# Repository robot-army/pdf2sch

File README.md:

# pdf2sch

Convert PDF schematics into KiCad schematics with a human-in-the-loop review loop.

## Current MVP

This repository now includes a minimal executable pipeline in `pdf2sch.py` that:

- Detects symbols/wires/text from a PDF source via a pluggable detector interface (placeholder for CV + OCR + ML)
- Filters likely sheet border/title block text
- Builds a structured component list + netlist
- Maps components to KiCad library symbols/footprint hints
- Prioritizes netlist correctness by asking review questions for low-confidence nets
- Generates KiCad schematic text output
- Preserves multi-page and hierarchical-sheet metadata in the generated schematic
- Uses a `PipelineConfig` object (uconfig-style declarative configuration) so detection/review/mapping rules can be tuned without changing core pipeline flow

## Run

```bash
cd <your-local-clone>/pdf2sch
python pdf2sch.py
```

Enter a PDF path or URL when prompted (for example the CN0359 PDF URL from the issue statement).

## Test

```bash
cd <your-local-clone>/pdf2sch
python -m unittest discover -s tests -v
```

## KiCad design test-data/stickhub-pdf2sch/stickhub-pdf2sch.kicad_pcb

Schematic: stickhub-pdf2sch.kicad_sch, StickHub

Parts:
C1: 1uF 10V; 1005_C; Voltage 16V; Tolerance 10%
C2, C5, C6, C7, C8, C9, C10, C11, C12, C13: 0.1uF; 1005_C; Voltage 16V; Tolerance 10%
C3, C4: 10uF 6.3V; 1005_C; Voltage 16V; Tolerance 10%
C14, C15, C16, C17, C18, C19, C20, C21: 0.1uF 100V; 2012_C; Voltage 16V; Tolerance 10%
C22, C23, C24, C25, C26, C27, C29, C30, C31, C32, C33, C34, C35, C36, C37: 22uF 10V; 1608_C; Voltage 16V; Tolerance 10%
C28: 15nF; 1005_C; Voltage 16V; Tolerance 10%
C38: 330uF 10V; CP_Elec_6.3x11_Board_Edge_Mirrored
D1, D2, D3, D4, D5, D6, D7, D8, D9, D10, D11, D12, D13, D14, D22, D23: TVS; D_0402; MPN AR0521P1
D15, D16, D17, D18, D19, D20, D21: USB; Duo_LED_1.6x0.8_Kingbright_APHB1608LZGKSURKC; MPN APHB1608SGEC
D24, D25: 5V; D_0402; MPN D5V0H1B2LP-7B
H1: Strap; Plain_Hole_3mm
J1: HOST; USB_A_PCB_traces_small
J2: USB1; JST_SH_SM04B-SRSS-TB_1x04-1MP_P1.00mm_Horizontal; MPN SM04B-SRSS-TB(LF)(SN)
J3: USB2; JST_SH_SM04B-SRSS-TB_1x04-1MP_P1.00mm_Horizontal; MPN SM04B-SRSS-TB(LF)(SN)
J4: USB3; JST_SH_SM04B-SRSS-TB_1x04-1MP_P1.00mm_Horizontal; MPN SM04B-SRSS-TB(LF)(SN)
J5: USB4; JST_SH_SM04B-SRSS-TB_1x04-1MP_P1.00mm_Horizontal; MPN SM04B-SRSS-TB(LF)(SN)
J6: USB5; JST_SH_SM04B-SRSS-TB_1x04-1MP_P1.00mm_Horizontal; MPN SM04B-SRSS-TB(LF)(SN)
J7: USB6; JST_SH_SM04B-SRSS-TB_1x04-1MP_P1.00mm_Horizontal; MPN SM04B-SRSS-TB(LF)(SN)
J8: USB7; JST_SH_SM04B-SRSS-TB_1x04-1MP_P1.00mm_Horizontal; MPN SM04B-SRSS-TB(LF)(SN)
J9: EXTGND; 1P-1.5x1.5
JP1: EXTPWR; JP-2_1.5x1.5
LOGO1: Logo; Creative_Commons_CC_Mask
LOGO2: Logo; Creative_Commons_BY_Mask
LOGO3: Logo; Creative_Commons_NC_Mask
LOGO4: Logo; Creative_Commons_SA_Mask
R1: 10k; R_1005_C; MPN 0402WGF1002TCE
R2, R3, R4, R5: 100k; R_1005_C; MPN 0402WGF1003TCE
R6: 2.7k; R_1005_C; MPN 0402WGF2701TCE
R7, R8, R9, R10, R11, R12, R13: 470; R_1005_C; MPN 0402WGF4700TCE
U1: MaxLinear_XR22417-48; LQFP-48_7x7mm_P0.5mm; MPN XR22417CV48TR-F
U2: Dialog_SLG5NT1487V; TDFN-8_1.5x2mm_Fused-Lead_JEDEC_MO-252_W2015D; MPN SLG5NT1487VTR
Y1: 12MHz 50ppm 16-20pF; Crystal_4-SMD_2.5x2mm; MPN CM4012M00020T8188026

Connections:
+1V8: C4.1, C11.1, C12.1, C13.1, U1.6 (VCC18), U1.21 (VCC18), U1.25 (1V8_OUT), U1.28 (VCC18)
+3.3V: C3.1, C5.1, C6.1, C7.1, C8.1, C9.1, C10.1, R3.1, R4.1, R5.1, U1.9 (3V3_OUT), U1.15 (VCC33), U1.20 (VCC33), U1.26 (VCC33), U1.31 (VCC33), U1.36 (VCC33), U1.42 (VCC33)
+5V: C1.1, C14.1, C15.1, C16.1, C17.1, C18.1, C19.1, C20.1, C22.1, C23.1, C24.1, C25.1, C26.1, C27.1, C29.1, C30.1, C31.1, C32.1, C33.1, C34.1, C35.1, C36.1, C37.1, C38.1 (+), D25.2 (A2), J2.1, J3.1, J4.1, J5.1, J6.1, J7.1, J8.1, R1.1, U1.8 (VCC5), U2.5 (S)
/D+: D23.2 (A2), J1.3, U1.30 (UP_D+)
/D-: D22.2 (A2), J1.2, U1.29 (UP_D-)
/LC: D15.GK (2), D15.RA (3), D16.GK (2), D16.RA (3), D17.GK (2), D17.RA (3), D18.GK (2), D18.RA (3), D19.GK (2), D19.RA (3), D20.GK (2), D20.RA (3), D21.GK (2), D21.RA (3), U1.1 (LED_CTL)
/LED1: R7.2, U1.3 (LED1/SCL)
/LED2: R8.2, U1.4 (LED2)
/LED3: R9.2, U1.5 (LED3)
/LED4: R10.2, U1.7 (LED4)
/LED5: R11.2, U1.48 (LED5)
/LED6: R12.2, U1.47 (LED6)
/LED7: R13.2, U1.46 (LED7)
/U1D+: D2.2 (A2), J2.3, U1.19 (USB1D+)
/U1D-: D1.2 (A2), J2.2, U1.18 (USB1D-)
/U2D+: D4.2 (A2), J3.3, U1.17 (USB2D+)
/U2D-: D3.2 (A2), J3.2, U1.16 (USB2D-)
/U3D+: D6.2 (A2), J4.3, U1.14 (USB3D+)
/U3D-: D5.2 (A2), J4.2, U1.13 (USB3D-)
/U4D+: D8.2 (A2), J5.3, U1.12 (USB4D+)
/U4D-: D7.2 (A2), J5.2, U1.11 (USB4D-)
/U5D+: D10.2 (A2), J6.3, U1.33 (USB5D+)
/U5D-: D9.2 (A2), J6.2, U1.32 (USB5D-)
/U6D+: D12.2 (A2), J7.3, U1.35 (USB6D+)
/U6D-: D11.2 (A2), J7.2, U1.34 (USB6D-)
/U7D+: D14.2 (A2), J8.3, U1.38 (USB7D+)
/U7D-: D13.2 (A2), J8.2, U1.37 (USB7D-)
/XI: U1.22 (XTALIN), Y1.1
/XO: U1.23 (XTALOUT), Y1.3
GND: C1.2, C2.2, C3.2, C4.2, C5.2, C6.2, C7.2, C8.2, C9.2, C10.2, C11.2, C12.2, C13.2, C14.2, C15.2, C16.2, C17.2, C18.2, C19.2, C20.2, C21.2, C22.2, C23.2, C24.2, C25.2, C26.2, C27.2, C28.2, C29.2, C30.2, C31.2, C32.2, C33.2, C34.2, C35.2, C36.2, C37.2, C38.2 (-), D1.1 (A1), D2.1 (A1), D3.1 (A1), D4.1 (A1), D5.1 (A1), D6.1 (A1), D7.1 (A1), D8.1 (A1), D9.1 (A1), D10.1 (A1), D11.1 (A1), D12.1 (A1), D13.1 (A1), D14.1 (A1), D22.1 (A1), D23.1 (A1), D24.1 (A1), D25.1 (A1), J1.4, J2.4, J2.MP (MountPin), J3.4, J3.MP (MountPin), J4.4, J4.MP (MountPin), J5.4, J5.MP (MountPin), J6.4, J6.MP (MountPin), J7.4, J7.MP (MountPin), J8.4, J8.MP (MountPin), J9.1, R2.2, R6.2, U1.10 (GND), U1.24 (GND), U1.39 (GND), U2.8 (GND), Y1.2 (GND), Y1.4 (GND)
unnamed: D15.GA (1), D15.RK (4), R7.1
unnamed: D16.GA (1), D16.RK (4), R8.1
unnamed: D17.GA (1), D17.RK (4), R9.1
unnamed: D18.GA (1), D18.RK (4), R10.1
unnamed: D19.GA (1), D19.RK (4), R11.1
unnamed: D20.GA (1), D20.RK (4), R12.1
unnamed: D21.GA (1), D21.RK (4), R13.1
unnamed: J1.1, JP1.1
unnamed: R3.2, U1.40 (EXT_RST#)
unnamed: R6.1, U1.27 (REXT)
unnamed: R5.2, U1.43 (TEST1#)
unnamed: R4.2, U1.45 (TEST3#)
unnamed: C2.1, R1.2, R2.1, U1.41 (VBUS_SENSE)
unnamed: C28.1, U2.7 (CAP)
VIN: C21.1, D24.2 (A2), JP1.2, U2.1 (VDD), U2.2 (ON), U2.3 (D)

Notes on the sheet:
ESD caps at connectors / plug
Shared VBUS capacitance

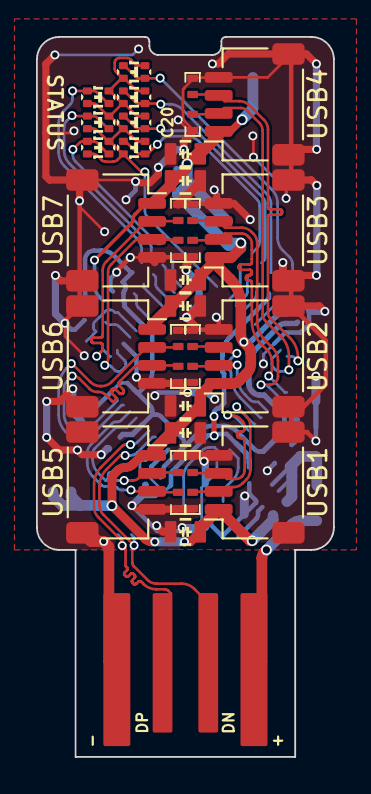
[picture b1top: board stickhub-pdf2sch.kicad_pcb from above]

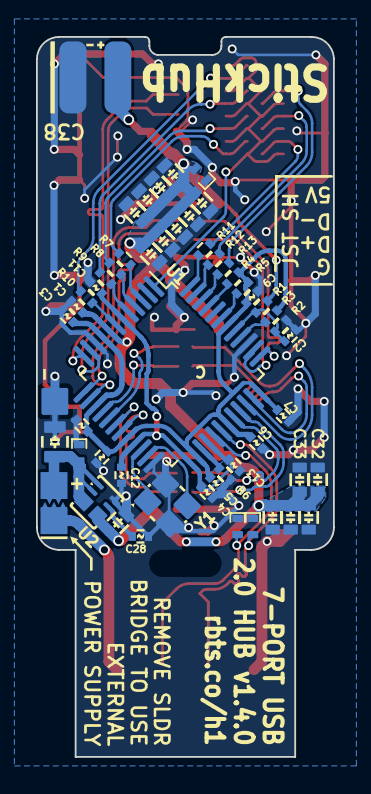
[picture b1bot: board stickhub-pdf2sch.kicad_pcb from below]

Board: 2 copper layers, 16.5 x 40.0 mm, 94 parts (57 on the bottom side), 45 nets.

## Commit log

2026-04-17 Initial plan
2026-04-17 feat: add initial PDF-to-KiCad pipeline MVP with review loop and tests
    Agent-Logs-Url: https://github.com/robot-army/pdf2sch/sessions/4d69907f-7b13-4efb-bc68-705c10b8a856
2026-04-17 feat: add uconfig-style pipeline configuration and clean cache artifacts
    Agent-Logs-Url: https://github.com/robot-army/pdf2sch/sessions/4d69907f-7b13-4efb-bc68-705c10b8a856
2026-04-17 fix: map review prompts to correct nets and clean README paths
    Agent-Logs-Url: https://github.com/robot-army/pdf2sch/sessions/4d69907f-7b13-4efb-bc68-705c10b8a856
2026-04-17 fix: improve symbol mapping using reference designators
    Agent-Logs-Url: https://github.com/robot-army/pdf2sch/sessions/4d69907f-7b13-4efb-bc68-705c10b8a856
2026-04-17 test: cover footprint fallback and refine default symbol mapping
    Agent-Logs-Url: https://github.com/robot-army/pdf2sch/sessions/4d69907f-7b13-4efb-bc68-705c10b8a856
2026-04-17 fix: validate review metadata alignment before prompting
    Agent-Logs-Url: https://github.com/robot-army/pdf2sch/sessions/4d69907f-7b13-4efb-bc68-705c10b8a856
2026-04-17 added test-data starting point
2026-04-17 added cn0359 sch as a proper test
2026-04-17 chore: plan real PDF detector for stickhub test case
    Agent-Logs-Url: https://github.com/robot-army/pdf2sch/sessions/b3ab281c-2bd9-408e-ba48-8c7ee96ff8a1
2026-04-17 feat: real PDF detector (Voronoi assignment), KiCad 9 plugin scaffold, CI with screenshots
    Agent-Logs-Url: https://github.com/robot-army/pdf2sch/sessions/b3ab281c-2bd9-408e-ba48-8c7ee96ff8a1
2026-04-17 fix: add pytest to CI deps; upgrade .kicad_sch to KiCad 9 format 20250114
    Agent-Logs-Url: https://github.com/robot-army/pdf2sch/sessions/442e95a9-22b2-4cc3-891f-30cd9354d4f5
2026-04-17 Fix CI pytest missing dep and KiCad 9 schematic load failures
    Agent-Logs-Url: https://github.com/robot-army/pdf2sch/sessions/c02145b0-1dfc-438c-a508-403e1e6d4f2a
2026-04-17 Plan: fix Device:Unknown symbol mismatch + add CI caching + TODOs
    Agent-Logs-Url: https://github.com/robot-army/pdf2sch/sessions/07a47a9c-c1c8-4fd0-8790-db0c70f779a0
2026-04-17 fix: Device:Unknown symbol name mismatch, add CI caching, add TODOs
    Agent-Logs-Url: https://github.com/robot-army/pdf2sch/sessions/07a47a9c-c1c8-4fd0-8790-db0c70f779a0
2026-04-17 fix: add requirements.txt so pip cache can compute its cache key
    Agent-Logs-Url: https://github.com/robot-army/pdf2sch/sessions/15109583-b2b1-45f1-8498-d90d080b2ffe
2026-04-17 fix: fix inner sub-symbol name in fallback lib definition for kicad-cli compatibility
    Agent-Logs-Url: https://github.com/robot-army/pdf2sch/sessions/5dcc2a9e-cde9-45b6-9b31-52f85452d873
2026-04-17 added realsmall testcase
2026-04-17 fix: realsmall-driven writer fixes + pin UUIDs derived from lib def, not hardcoded table
    Agent-Logs-Url: https://github.com/robot-army/pdf2sch/sessions/e9467aa7-85bc-429a-86cf-4c253f3f1f27
2026-04-17 feat: stickhub+cn0359 support — guess_symbol expansion, ref dedup, adaptive grid, kicad_sym library reader, new stubs
    Agent-Logs-Url: https://github.com/robot-army/pdf2sch/sessions/11deefbf-2e2c-4dc8-a50a-62932d8e5bf1
2026-04-17 fix: generate .kicad_pro alongside .kicad_sch so kicad-cli can load schematic (exit code 3 fix)
    Agent-Logs-Url: https://github.com/robot-army/pdf2sch/sessions/fbce35b3-1107-4358-8a58-f43406d173d2
2026-04-17 fix: use project name in instances block so kicad-cli can load schematic
    Agent-Logs-Url: https://github.com/robot-army/pdf2sch/sessions/bbc787a2-7df8-486d-96c4-f21f0edfccb8
2026-04-17 ci: add auto-approve workflow for copilot-swe-agent[bot] runs
    Agent-Logs-Url: https://github.com/robot-army/pdf2sch/sessions/31c2e787-1205-4f37-b89e-ac27be809dc1
2026-04-17 Fix global_label format: text as direct string not (text ...) sub-expression
    KiCad's schematic parser (parseSchText) calls NeedSYMBOL() immediately
    after consuming the 'global_label' token, expecting the label text as a
    direct quoted string. The previous code emitted:
    (global_label
    (text "+5V")
    ...
2026-04-17 fix(pdf_detector): proximity+topology filter cuts wire noise; fix GND detection
    - Add _filter_segs_by_anchors(): BFS from segments near components/labels;
    eliminates border-grid lines and isolated symbol decorations without
    relying on colour — works for any PDF including B&W.
    - Add _UF_MIN_SEG_LEN_PT=9: only segments ≥9pt join the union-find topology
    so short symbol-body stubs cannot bridge separate nets (fixes R1 incorrectly
    appearing in +5V net for realsmall; short pin stubs still register via
2026-04-17 feat: place components at PDF positions, emit real wires, fix label placement
    - pdf2sch.py: add x_pts/y_pts/pin_axis to DetectedSymbol; x_mm/y_mm/angle to
    Component; label_x_pts/y_pts/angle to DetectedWire; label_x_mm/y_mm/angle to
    Net; wire_segments to DetectionOutput and SchematicModel; _snap_mm/_comp_angle
    helpers; _make_component() in build_model()
    - pdf_detector.py: _infer_component_centers_and_axes() uses closest wire
    endpoint per segment to find exact component center + H/V pin axis;
2026-04-17 ci: embed PNG screenshots as base64 in job summary for inline mobile viewing
    After PNG conversion, a new "Write inline image summary" step encodes each
    screenshot as base64 and writes <img src="data:image/png;base64,..."> tags to
    $GITHUB_STEP_SUMMARY. The Actions summary page then renders all schematics
    inline — no zip download required, works in Chrome on Android.
    PNGs are also capped at 1200px wide (-resize '1200x>') to stay well within
    the 1 MB GitHub summary file limit while still being readable on mobile.
2026-04-18 docs: add AGENT_NOTES.md with strategy, current status, gaps, and local dev guide
    Agent-Logs-Url: https://github.com/robot-army/pdf2sch/sessions/a1d07a91-2883-4e66-8fac-5f714f7e2ff9
